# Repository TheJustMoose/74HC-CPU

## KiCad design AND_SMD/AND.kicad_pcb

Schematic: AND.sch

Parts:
C1: 0.1uF; C_0805_2012Metric_Pad1.18x1.45mm_HandSolder
D1: LED; LED_0805_2012Metric_Pad1.15x1.40mm_HandSolder
J1, J2, J3: Conn_01x08_Male; PinHeader_1x08_P2.54mm_Vertical
J4: Conn_01x04_Male; PinHeader_1x04_P2.54mm_Vertical
R1: 1k; R_0805_2012Metric_Pad1.20x1.40mm_HandSolder
U1: 74LS573; SOP-20_7.5x12.8mm_P1.27mm
U2, U3: 74LS08; SO-14_3.9x8.65mm_P1.27mm

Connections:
/A0: J2.8, U2.1
/A7: J2.1, U3.10
/B0: J1.8, U2.2
/B7: J1.1, U3.9
/Latch: J4.4, U1.11 (Load)
/OUT0: J3.8, U1.12 (Q7)
/OUT7: J3.1, U1.19 (Q0)
/~OE: J4.1, R1.2, U1.1 (OE)
GND: C1.2, J4.2, U1.10 (GND), U2.7 (GND), U3.7 (GND)
unnamed: D1.1, R1.1
unnamed: J1.2, U3.12
unnamed: J1.3, U3.4
unnamed: J1.4, U3.1
unnamed: J1.5, U2.9
unnamed: J1.6, U2.12
unnamed: J1.7, U2.4
unnamed: J2.2, U3.13
unnamed: J2.3, U3.5
unnamed: J2.4, U3.2
unnamed: J2.5, U2.10
unnamed: J2.6, U2.13
unnamed: J2.7, U2.5
unnamed: J3.2, U1.18 (Q1)
unnamed: J3.3, U1.17 (Q2)
unnamed: J3.4, U1.16 (Q3)
unnamed: J3.5, U1.15 (Q4)
unnamed: J3.6, U1.14 (Q5)
unnamed: J3.7, U1.13 (Q6)
unnamed: U1.2 (D0), U3.8
unnamed: U1.3 (D1), U3.11
unnamed: U1.4 (D2), U3.6
unnamed: U1.5 (D3), U3.3
unnamed: U1.6 (D4), U2.8
unnamed: U1.7 (D5), U2.11
unnamed: U1.8 (D6), U2.6
unnamed: U1.9 (D7), U2.3
VCC: C1.1, D1.2, J4.3, U1.20 (VCC), U2.14 (VCC), U3.14 (VCC)

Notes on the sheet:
Out
Ctrl

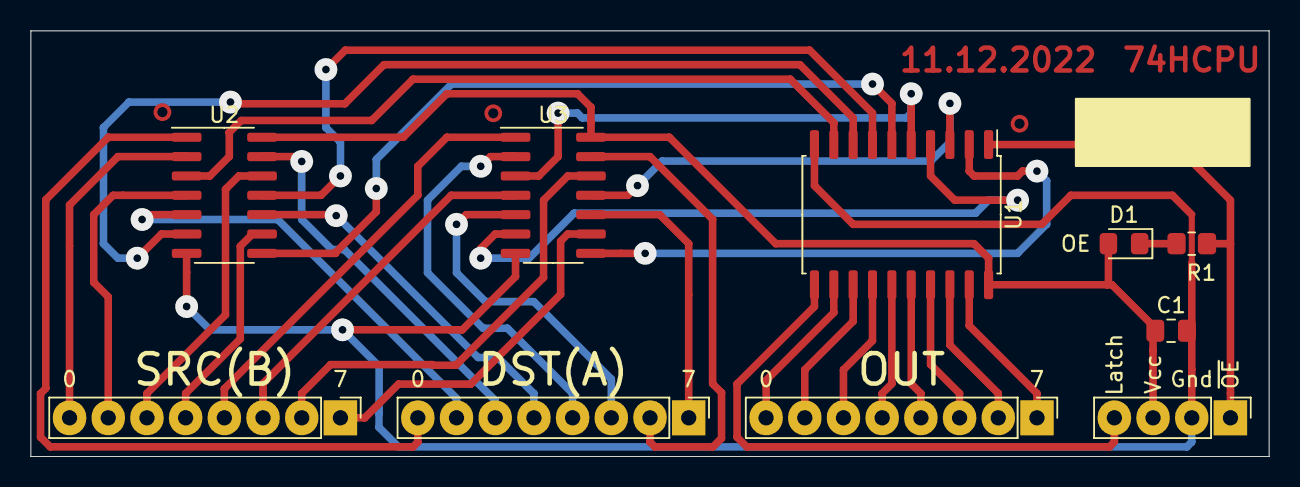
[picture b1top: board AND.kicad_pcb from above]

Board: 2 copper layers, 81.3 x 27.9 mm, 10 parts (0 on the bottom side), 37 nets.

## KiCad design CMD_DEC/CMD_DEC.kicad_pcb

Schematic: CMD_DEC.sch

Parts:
C1, C3, C4, C5, C6: 0.1uF; C_0805_2012Metric_Pad1.18x1.45mm_HandSolder
D1: LED; LED_D5.0mm
H1, H2, H3: MountingHole; MountingHole_3.2mm_M3
J1, J16: Conn_01x04_Male; PinHeader_1x04_P2.54mm_Vertical
J2, J7, J8, J9, J10, J11, J12, J13, J17, J18: Conn_01x01_Male; PinHeader_1x01_P2.54mm_Vertical
J3: Conn_01x05_Male; PinHeader_1x05_P2.54mm_Vertical
J4, J5: Conn_01x08_Male; PinHeader_1x08_P2.54mm_Vertical
J6: Conn_01x02_Male; PinHeader_1x02_P2.54mm_Vertical
J14: Screw_Terminal_01x02; TerminalBlock_Phoenix_MKDS-1,5-2_1x02_P5.00mm_Horizontal
J15: Conn_01x03_Male; PinHeader_1x03_P2.54mm_Vertical
R1, R2: 10k; R_0805_2012Metric_Pad1.20x1.40mm_HandSolder
R5: 1k; R_0805_2012Metric_Pad1.20x1.40mm_HandSolder
U1: 74LS08; DIP-14_W7.62mm_Socket
U2, U4: 74LS138; DIP-16_W7.62mm_Socket
U3: 74LS139; DIP-16_W7.62mm_Socket
U5: 74LS85; DIP-16_W7.62mm_Socket
U6: 74HC00; DIP-14_W7.62mm_Socket

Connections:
/C1: J2.1, U2.5 (E2), U4.5 (E2)
/C2: J13.1, U1.2, U6.10
/CF_EN: J12.1, U6.3
/CMP_EN: J11.1, U6.6
/COP[0]: J1.1, U2.1 (A0), U4.1 (A0), U5.10 (A0)
/COP[1]: J1.2, U2.2 (A1), U4.2 (A1), U5.12 (A1)
/COP[2]: J1.3, U2.3 (A2), U4.3 (A2), U5.13 (A2)
/COP[3]: J1.4, U2.4 (E1), U4.6 (E3), U5.15 (A3)
/LATCH_REG: J8.1, U1.3
/SRC[0]: J6.1, U3.14 (A0)
/SRC[1]: J6.2, U3.13 (A1)
/WILL_WR2REG: J18.1, R5.1, U1.1, U5.7 (Oa<b)
/~ADD: J4.1, U1.4, U2.15 (O0)
/~ADDC: J4.2, U1.5, U2.14 (O1)
/~ADDx: J9.1, U1.6, U6.1
/~AND: J4.3, U2.13 (O2)
/~BRANCH: J5.8, U4.7 (O7)
/~CMP: J5.7, U4.9 (O6), U6.4, U6.5
/~CTRL: J5.6, U4.10 (O5)
/~IN: J5.3, U4.13 (O2)
/~INV: J3.1, U3.12 (O0)
/~LD: J5.2, J17.1, U1.9, U4.14 (O1)
/~LDI: J5.1, U4.15 (O0)
/~LSR: J3.3, U1.13, U3.10 (O2)
/~LSRC: J3.4, U1.12, U3.9 (O3)
/~LSRx: J3.5, U1.11, U6.2
/~MOV: J4.7, U2.9 (O6)
/~MUL: J4.8, U2.7 (O7); also elsewhere on the board
/~OR: J4.4, U2.12 (O3)
/~OUT: J5.4, U4.12 (O3)
/~RAM_CS: J7.1, U1.8
/~RAM_WR: J10.1, U6.8
/~ST: J5.5, U1.10, U4.11 (O4), U6.12, U6.13
/~SWAP: J3.2, U3.11 (O1)
/~UNO: J4.6, U2.10 (O5), U3.15 (E)
/~XOR: J4.5, U2.11 (O4)
GND: C1.2, C3.2, C4.2, C5.2, C6.2, D1.1 (K), J14.2, U1.7 (GND), U2.8 (GND), U3.8 (GND), U4.4 (E1), U4.8 (GND), U5.2 (Ia<b), U5.4 (Ia>b), U5.8 (GND), U5.14 (B2), U6.7 (GND)
unnamed: D1.2 (A), R5.2
unnamed: J15.1, U3.3 (A1)
unnamed: J15.2, U3.2 (A0)
unnamed: J15.3, U3.1 (E)
unnamed: J16.1, U3.4 (O0)
unnamed: J16.2, U3.5 (O1)
unnamed: J16.3, U3.6 (O2)
unnamed: J16.4, U3.7 (O3)
unnamed: R1.1, U2.6 (E3)
unnamed: R2.1, U5.1 (B3), U5.3 (Ia=b), U5.9 (B0), U5.11 (B1)
unnamed: U6.9, U6.11
VCC: C1.1, C3.1, C4.1, C5.1, C6.1, J14.1, R1.2, R2.2, U1.14 (VCC), U2.16 (VCC), U3.16 (VCC), U4.16 (VCC), U5.16 (VCC), U6.14 (VCC)

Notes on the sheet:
< 1011
Signal C1 temporarily disables the outputs to avoid short circuits on commands outputs.
1011

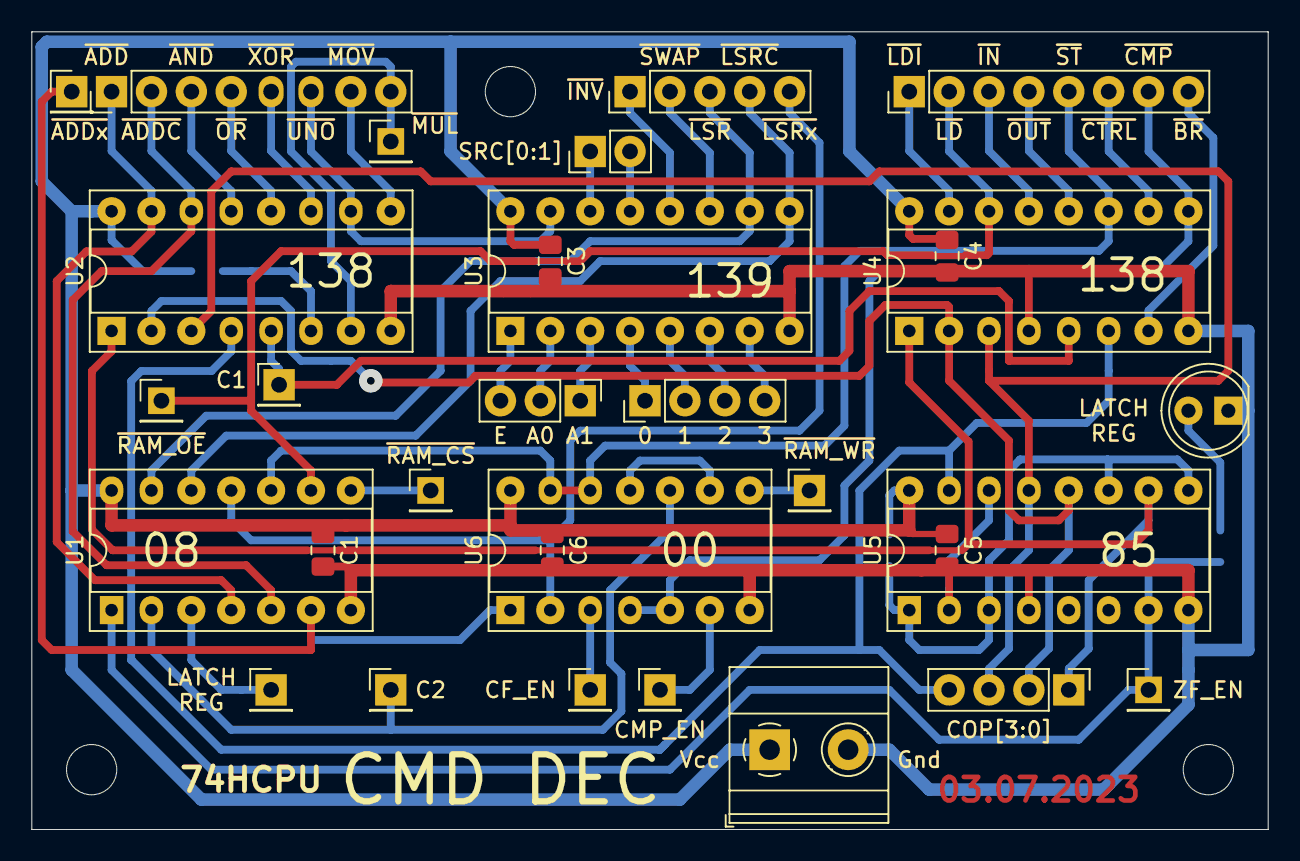
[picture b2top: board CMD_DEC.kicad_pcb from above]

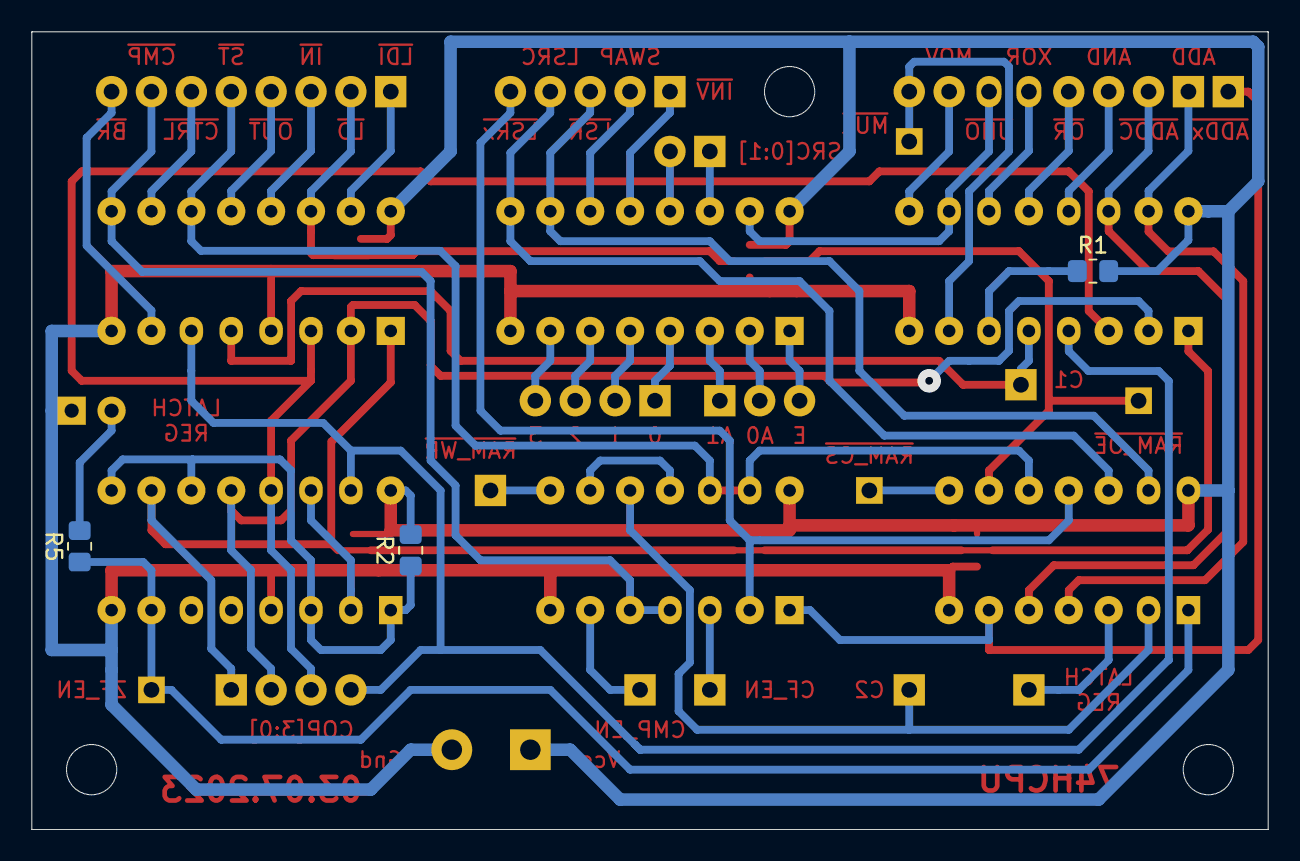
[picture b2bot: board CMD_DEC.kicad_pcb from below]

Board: 2 copper layers, 78.7 x 50.8 mm, 37 parts (3 on the bottom side), 49 nets.

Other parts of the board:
J19: Conn_01x01_Male; PinHeader_1x01_P2.54mm_Vertical

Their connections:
/~MUL: J19.1; also elsewhere on the board

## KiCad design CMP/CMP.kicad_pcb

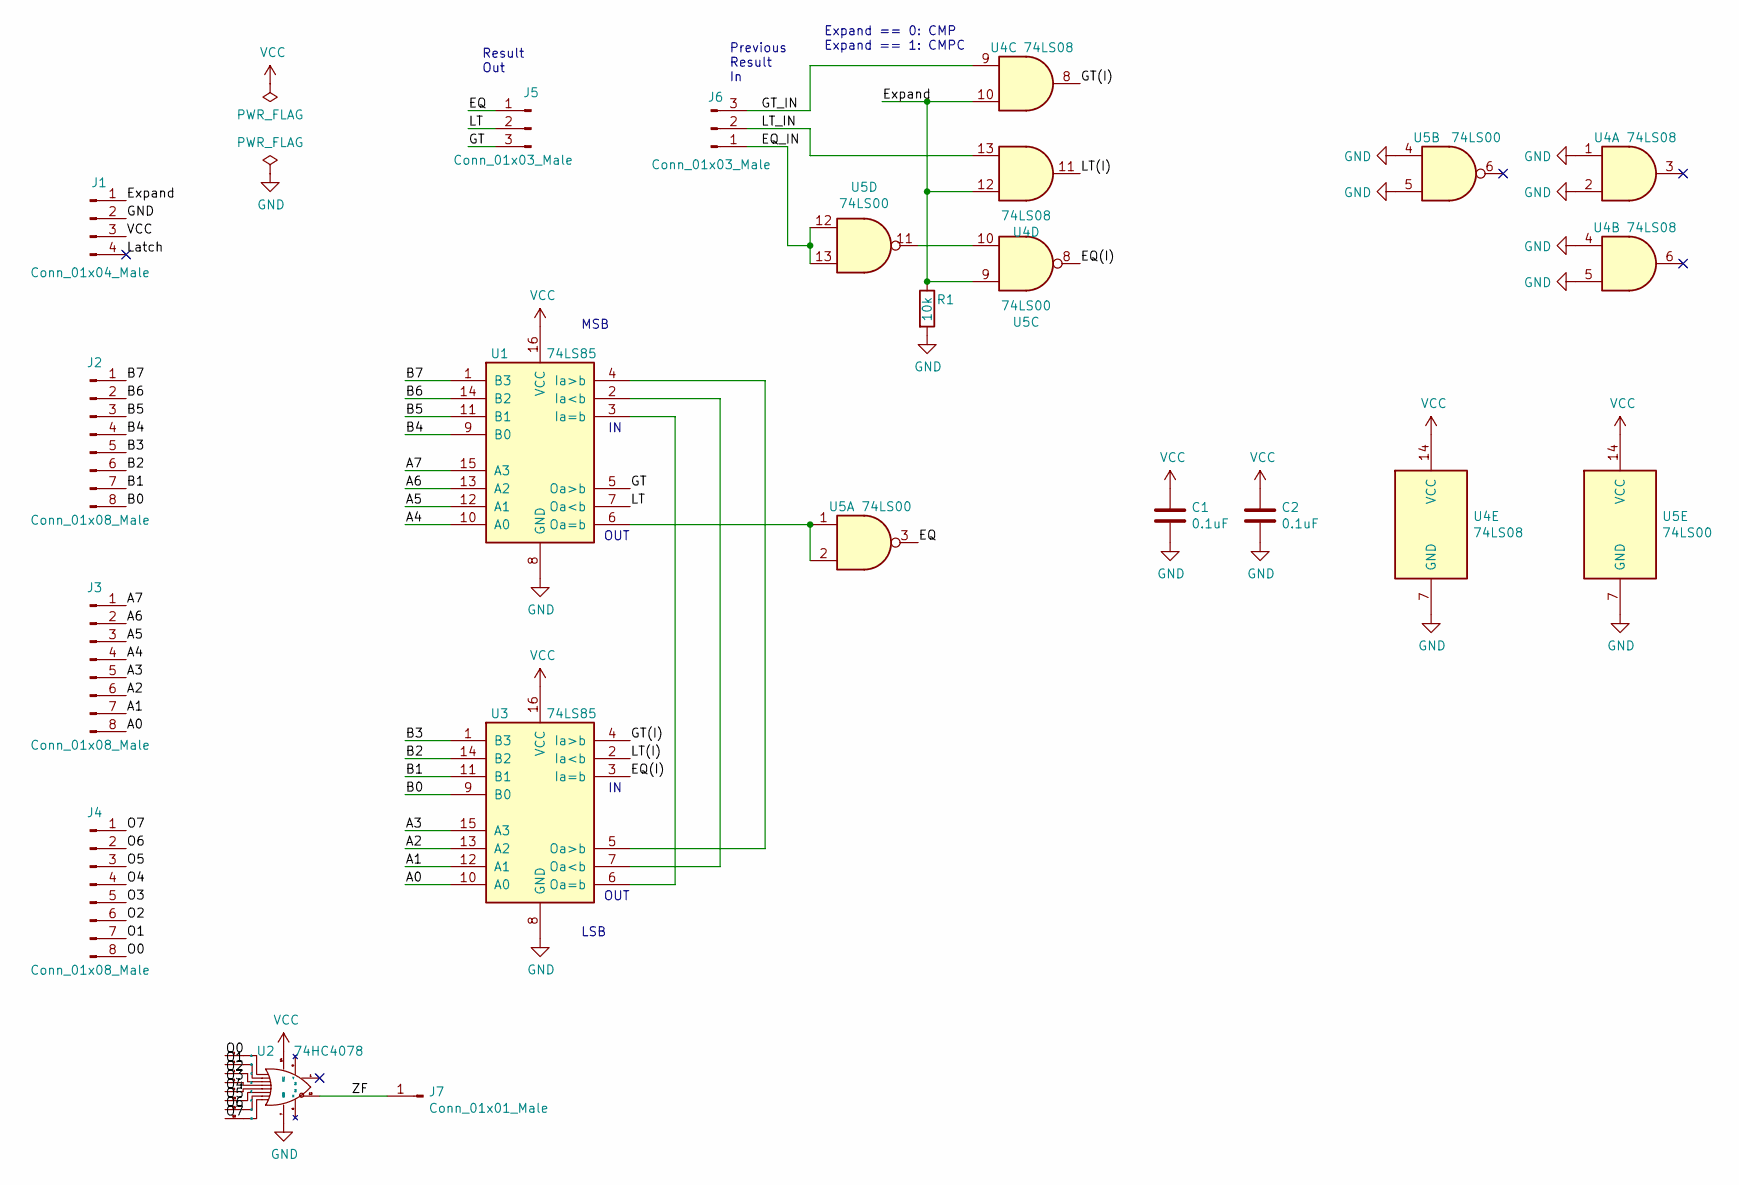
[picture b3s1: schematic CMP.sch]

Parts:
C1, C2: 0.1uF; C_Axial_L3.8mm_D2.6mm_P12.50mm_Horizontal
J1: Conn_01x04_Male; PinHeader_1x04_P2.54mm_Horizontal
J2, J3, J4: Conn_01x08_Male; PinHeader_1x08_P2.54mm_Horizontal
J5, J6: Conn_01x03_Male; PinHeader_1x03_P2.54mm_Horizontal
J7: Conn_01x01_Male; PinHeader_1x01_P2.54mm_Horizontal
R1: 10k; R_0805_2012Metric_Pad1.20x1.40mm_HandSolder
U1, U3: 74LS85; SO-16_3.9x9.9mm_P1.27mm
U2: 74HC4078; SO-14_3.9x8.65mm_P1.27mm
U4: 74LS08; SO-14_3.9x8.65mm_P1.27mm
U5: 74LS00; SO-14_3.9x8.65mm_P1.27mm

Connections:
/A0: J3.8, U3.10 (A0)
/A1: J3.7, U3.12 (A1)
/A2: J3.6, U3.13 (A2)
/A3: J3.5, U3.15 (A3)
/A4: J3.4, U1.10 (A0)
/A5: J3.3, U1.12 (A1)
/A6: J3.2, U1.13 (A2)
/A7: J3.1, U1.15 (A3)
/B0: J2.8, U3.9 (B0)
/B1: J2.7, U3.11 (B1)
/B2: J2.6, U3.14 (B2)
/B3: J2.5, U3.1 (B3)
/B4: J2.4, U1.9 (B0)
/B5: J2.3, U1.11 (B1)
/B6: J2.2, U1.14 (B2)
/B7: J2.1, U1.1 (B3)
/EQ: J5.1, U5.3
/EQ(I): U3.3 (Ia=b), U5.8
/EQ_IN: J6.1, U5.12, U5.13
/Expand: J1.1, R1.1, U4.10, U4.12, U5.9
/GT: J5.3, U1.5 (Oa>b)
/GT(I): U3.4 (Ia>b), U4.8
/GT_IN: J6.3, U4.9
/LT: J5.2, U1.7 (Oa<b)
/LT(I): U3.2 (Ia<b), U4.11
/LT_IN: J6.2, U4.13
/Latch: J1.4
/O0: J4.8, U2.2 (A)
/O1: J4.7, U2.3 (B)
/O2: J4.6, U2.4 (C)
/O3: J4.5, U2.5 (D)
/O4: J4.4, U2.9 (E)
/O5: J4.3, U2.10 (F)
/O6: J4.2, U2.11 (G)
/O7: J4.1, U2.12 (H)
/ZF: J7.1, U2.13 (X)
GND: C1.2, C2.2, J1.2, R1.2, U1.8 (GND), U2.7 (GND), U3.8 (GND), U4.1, U4.2, U4.4, U4.5, U4.7 (GND), U5.4, U5.5, U5.7 (GND)
unnamed: U1.2 (Ia<b), U3.7 (Oa<b)
unnamed: U1.3 (Ia=b), U3.6 (Oa=b)
unnamed: U1.4 (Ia>b), U3.5 (Oa>b)
unnamed: U1.6 (Oa=b), U5.1, U5.2
unnamed: U5.10, U5.11
VCC: C1.1, C2.1, J1.3, U1.16 (VCC), U2.14 (VCC), U3.16 (VCC), U4.14 (VCC), U5.14 (VCC)

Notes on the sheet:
LSB
MSB
OUT
Result Out
Previous Result In
Expand == 0: CMP Expand == 1: CMPC

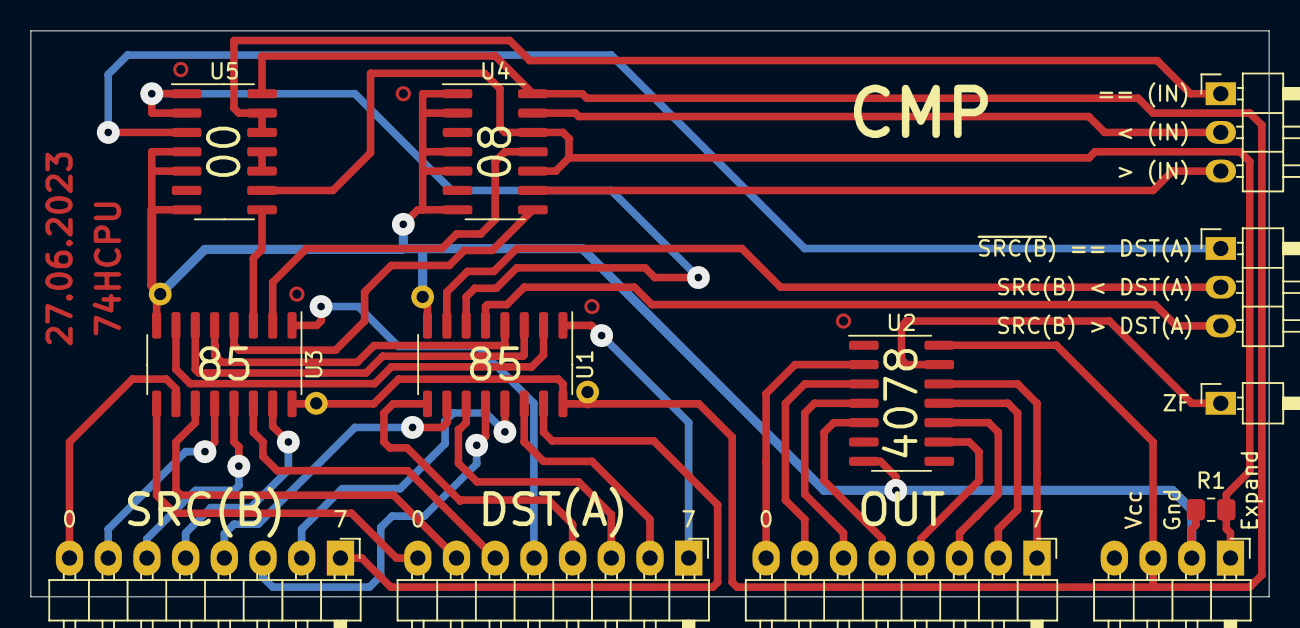
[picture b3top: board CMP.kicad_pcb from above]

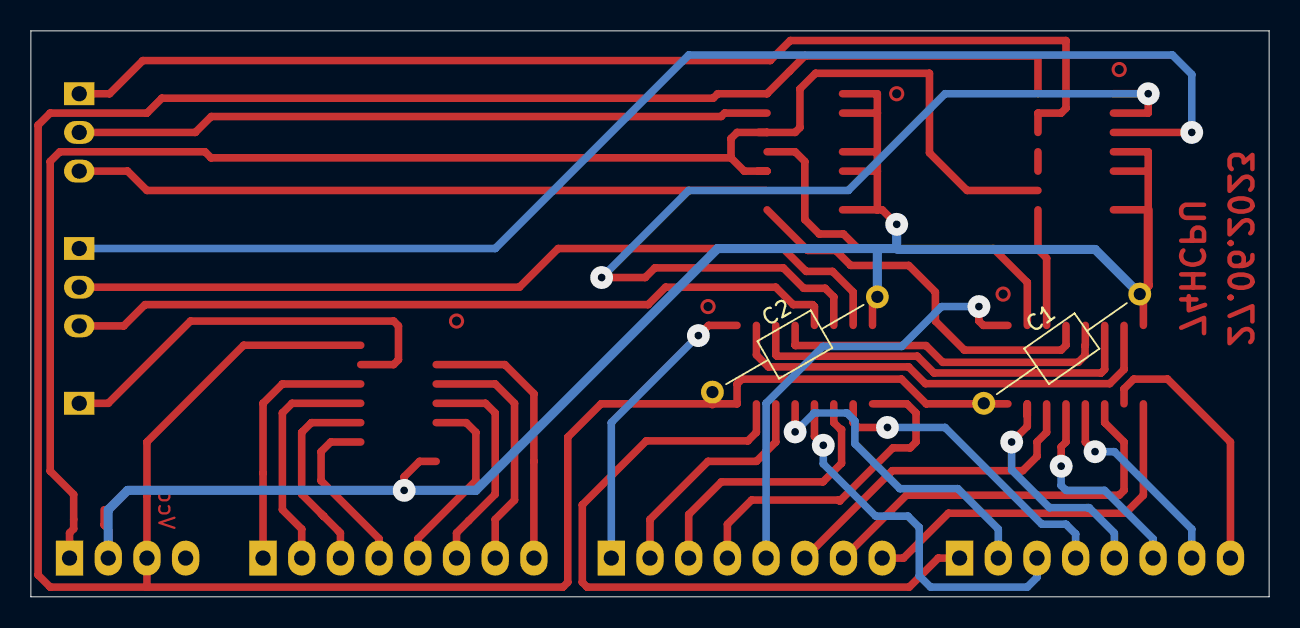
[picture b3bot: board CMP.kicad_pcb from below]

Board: 2 copper layers, 81.3 x 37.1 mm, 15 parts (2 on the bottom side), 42 nets.

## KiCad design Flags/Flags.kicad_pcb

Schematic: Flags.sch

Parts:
C1, C2: 0.1uF; C_Axial_L5.1mm_D3.1mm_P12.50mm_Horizontal
C3: 0.1uF; C_Axial_L5.1mm_D3.1mm_P15.00mm_Horizontal
D1, D2, D3, D4, D5: LED; LED_Rectangular_W5.0mm_H2.0mm
H1, H2, H3, H4: MountingHole; MountingHole_3.2mm_M3
J1: Conn_01x07_Male; PinHeader_1x07_P2.54mm_Vertical
J2: Conn_01x06_Male; PinHeader_1x06_P2.54mm_Vertical
J3: Conn_01x03_Male; PinHeader_1x03_P2.54mm_Vertical
J4, J5, J6, J7: Conn_01x01_Male; PinHeader_1x01_P2.54mm_Vertical
J8: Conn_01x02_Male; PinHeader_1x02_P2.54mm_Vertical
R1, R3: 10k; R_Axial_DIN0207_L6.3mm_D2.5mm_P7.62mm_Horizontal
R2, R4, R5, R6, R7: 1k; R_0805_2012Metric_Pad1.20x1.40mm_HandSolder
U1: 74LS08; DIP-14_W7.62mm_Socket
U2: 74HC74; DIP-14_W7.62mm_Socket
U3: 74LS175; DIP-16_W7.62mm_Socket

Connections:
/C2: J7.1, U1.2, U1.5, U1.10
/CF: J1.5, J5.1, J6.1, U2.6 (~Q)
/CF_EN: J3.1, U1.9
/CMP_EN: J3.3, U1.1
/EQ: J1.3, U3.3 (~Q0)
/GT: J1.2, U3.10 (Q2)
/GT_IN: J2.6, U3.12 (D2)
/LT: J1.1, U3.7 (Q1)
/LT_IN: J2.5, U3.5 (D1)
/ZF: J1.7, U2.9 (Q)
/ZF_EN: J3.2, U1.4
/ZF_IN: J2.3, U2.12 (D)
/~CF: D1.1 (K), J1.4, U2.5 (Q)
/~CF1_IN: J2.1, U1.12
/~CF2_IN: J2.2, U1.13
/~EQ: D4.1 (K), U3.2 (Q0)
/~EQ_IN: J2.4, U3.4 (D0)
/~GT: D5.1 (K), U3.11 (~Q2)
/~LT: D3.1 (K), U3.6 (~Q1)
/~RES_FL: J4.1, U2.4 (~S), U2.13 (~R), U3.1 (~Mr)
/~ZF: D2.1 (K), J1.6, U2.8 (~Q)
GND: C1.2, C2.2, C3.2, J8.2, U1.7 (GND), U2.7 (GND), U3.8 (GND), U3.13 (D3)
unnamed: D1.2 (A), R2.2
unnamed: D2.2 (A), R4.2
unnamed: D3.2 (A), R5.2
unnamed: D4.2 (A), R6.2
unnamed: D5.2 (A), R7.2
unnamed: R1.1, U2.1 (~R)
unnamed: R3.2, U2.10 (~S)
unnamed: U1.3, U3.9 (Cp)
unnamed: U1.6, U2.11 (C)
unnamed: U1.8, U2.3 (C)
unnamed: U1.11, U2.2 (D)
VCC: C1.1, C2.1, C3.1, J8.1, R1.2, R2.1, R3.1, R4.1, R5.1, R6.1, R7.1, U1.14 (VCC), U2.14 (VCC), U3.16 (VCC)

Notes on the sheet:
При сбросе триггера на всех выходах появляется 0. Однако, при сравнении чисел хотя бы один выход должен быть 1! Поэтому выход EQ инвертируется на выходе схемы сравнения.
ADD cmd
LSR cmd
Pins may be connected to:
Inverted CF
Back to the commands: ADD, LSR

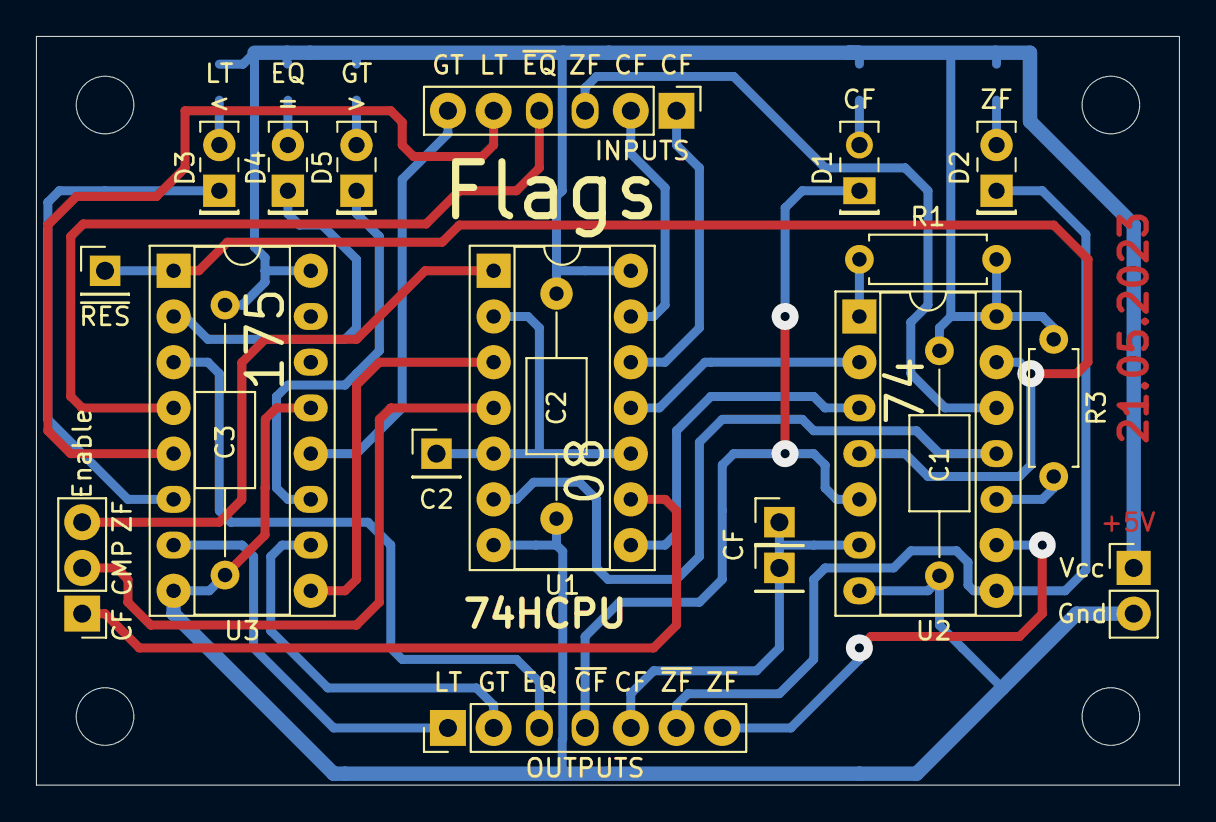
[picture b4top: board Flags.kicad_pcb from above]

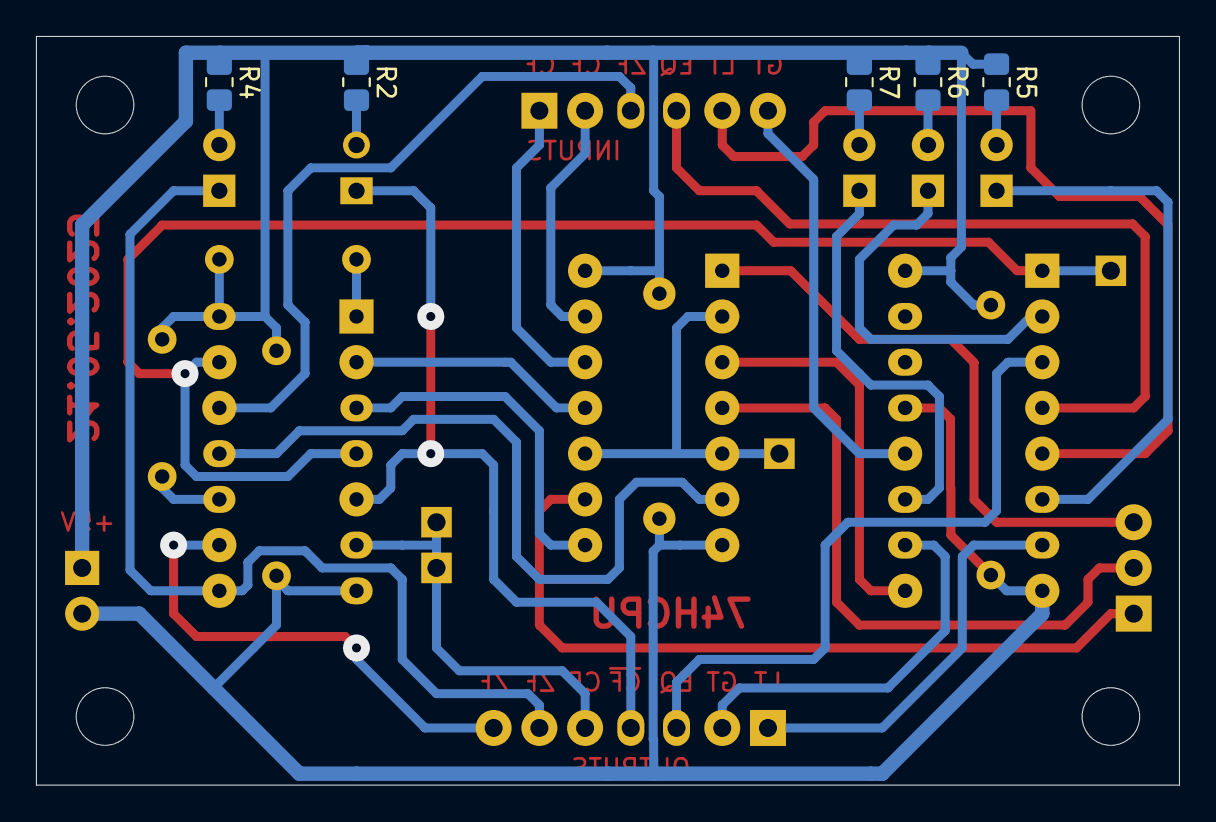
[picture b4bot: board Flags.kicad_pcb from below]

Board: 2 copper layers, 63.5 x 41.6 mm, 30 parts (5 on the bottom side), 34 nets.

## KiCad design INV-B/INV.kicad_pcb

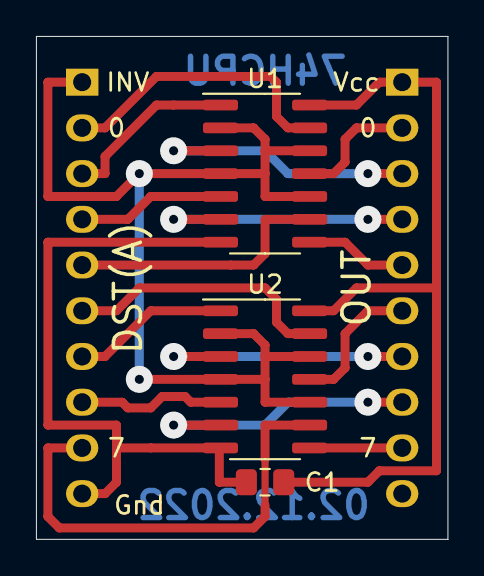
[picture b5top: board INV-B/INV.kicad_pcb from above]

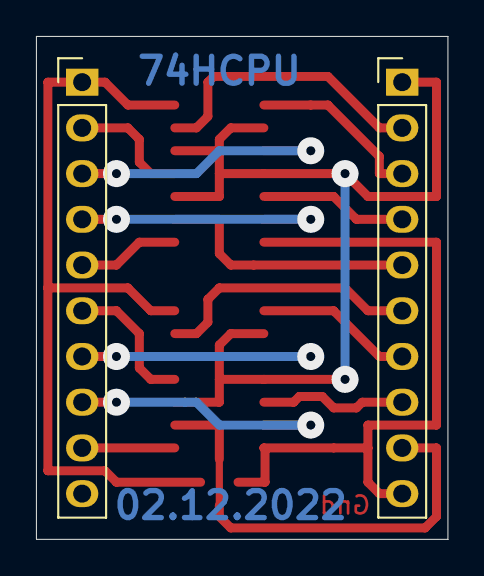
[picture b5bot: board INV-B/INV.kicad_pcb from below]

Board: 2 copper layers, 22.9 x 27.9 mm, 5 parts (2 on the bottom side), 19 nets.

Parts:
C1: 0.1uF; C_0805_2012Metric_Pad1.18x1.45mm_HandSolder
J1, J2: Conn_01x10_Male; PinHeader_1x10_P2.54mm_Vertical
U1, U2: 74HC86; SO-14_3.9x8.65mm_P1.27mm

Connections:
/D0: J1.2, U1.13
/D1: J1.3, U1.1
/D2: J1.4, U1.5
/D3: J1.5, U1.9
/D4: J1.6, U2.13
/D5: J1.7, U2.1
/D6: J1.8, U2.5
/D7: J1.9, U2.9
/INV: J1.1, U1.2, U1.4, U1.10, U1.12, U2.2, U2.4, U2.10, U2.12
/O0: J2.2, U1.11
/O1: J2.3, U1.3
/O2: J2.4, U1.6
/O3: J2.5, U1.8
/O4: J2.6, U2.11
/O5: J2.7, U2.3
/O6: J2.8, U2.6
/O7: J2.9, U2.8
GND: C1.2, J1.10, U1.7, U2.7
VCC: C1.1, J2.1, U1.14, U2.14

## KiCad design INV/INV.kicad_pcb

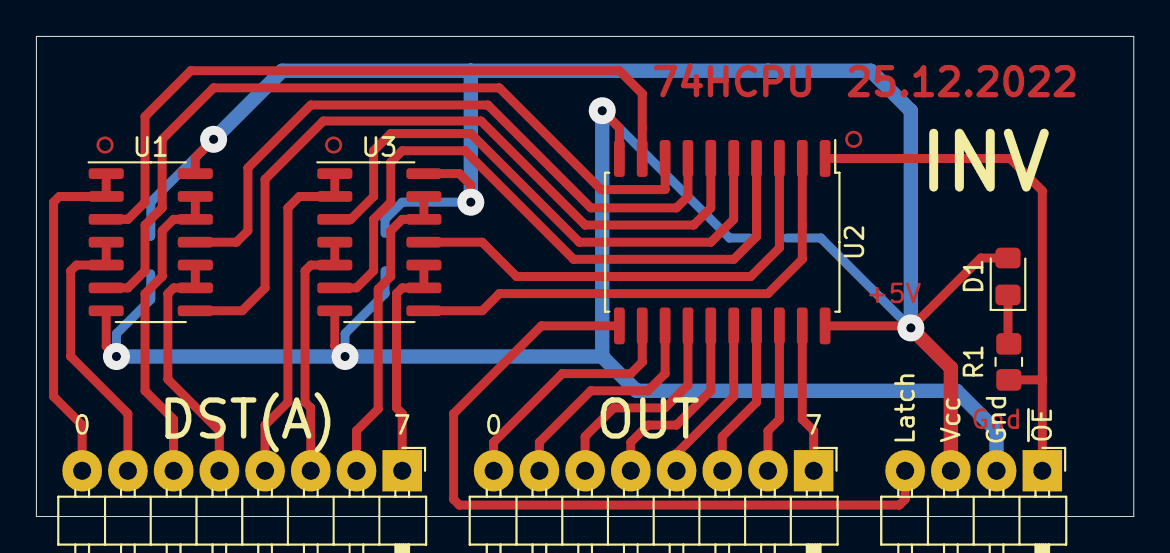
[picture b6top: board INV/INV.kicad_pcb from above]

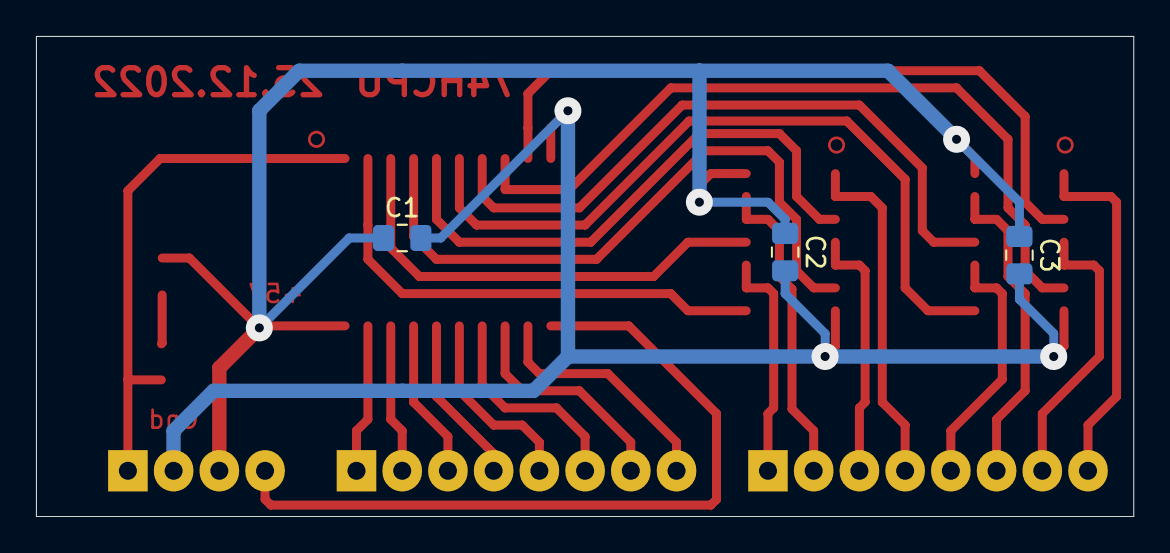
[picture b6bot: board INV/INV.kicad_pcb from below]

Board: 2 copper layers, 61.0 x 26.7 mm, 11 parts (3 on the bottom side), 29 nets.

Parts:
C1, C2, C3: 0.1uF; C_0805_2012Metric_Pad1.18x1.45mm_HandSolder
D1: LED; LED_0805_2012Metric_Pad1.15x1.40mm_HandSolder
J1, J2: Conn_01x08_Male; PinHeader_1x08_P2.54mm_Horizontal
J3: Conn_01x04_Male; PinHeader_1x04_P2.54mm_Horizontal
R1: 1k; R_0805_2012Metric_Pad1.20x1.40mm_HandSolder
U1, U3: 74HC00; SO-14_3.9x8.65mm_P1.27mm
U2: 74LS573; SOIC-20W_7.5x12.8mm_P1.27mm

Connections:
/Latch: J3.4, U2.11
/O0: J2.8, U2.12
/O1: J2.7, U2.13
/O2: J2.6, U2.14
/O3: J2.5, U2.15
/O4: J2.4, U2.16
/O5: J2.3, U2.17
/O6: J2.2, U2.18
/O7: J2.1, U2.19
/~OE: J3.1, R1.2, U2.1
GND: C1.2, C2.2, C3.2, J3.2, U1.7, U2.10, U3.7
unnamed: D1.1, R1.1
unnamed: J1.1, U3.9, U3.10
unnamed: J1.2, U3.12, U3.13
unnamed: J1.3, U3.4, U3.5
unnamed: J1.4, U3.1, U3.2
unnamed: J1.5, U1.9, U1.10
unnamed: J1.6, U1.12, U1.13
unnamed: J1.7, U1.4, U1.5
unnamed: J1.8, U1.1, U1.2
unnamed: U1.3, U2.9
unnamed: U1.6, U2.8
unnamed: U1.8, U2.6
unnamed: U1.11, U2.7
unnamed: U2.2, U3.8
unnamed: U2.3, U3.11
unnamed: U2.4, U3.6
unnamed: U2.5, U3.3
VCC: C1.1, C2.1, C3.1, D1.2, J3.3, U1.14, U2.20, U3.14

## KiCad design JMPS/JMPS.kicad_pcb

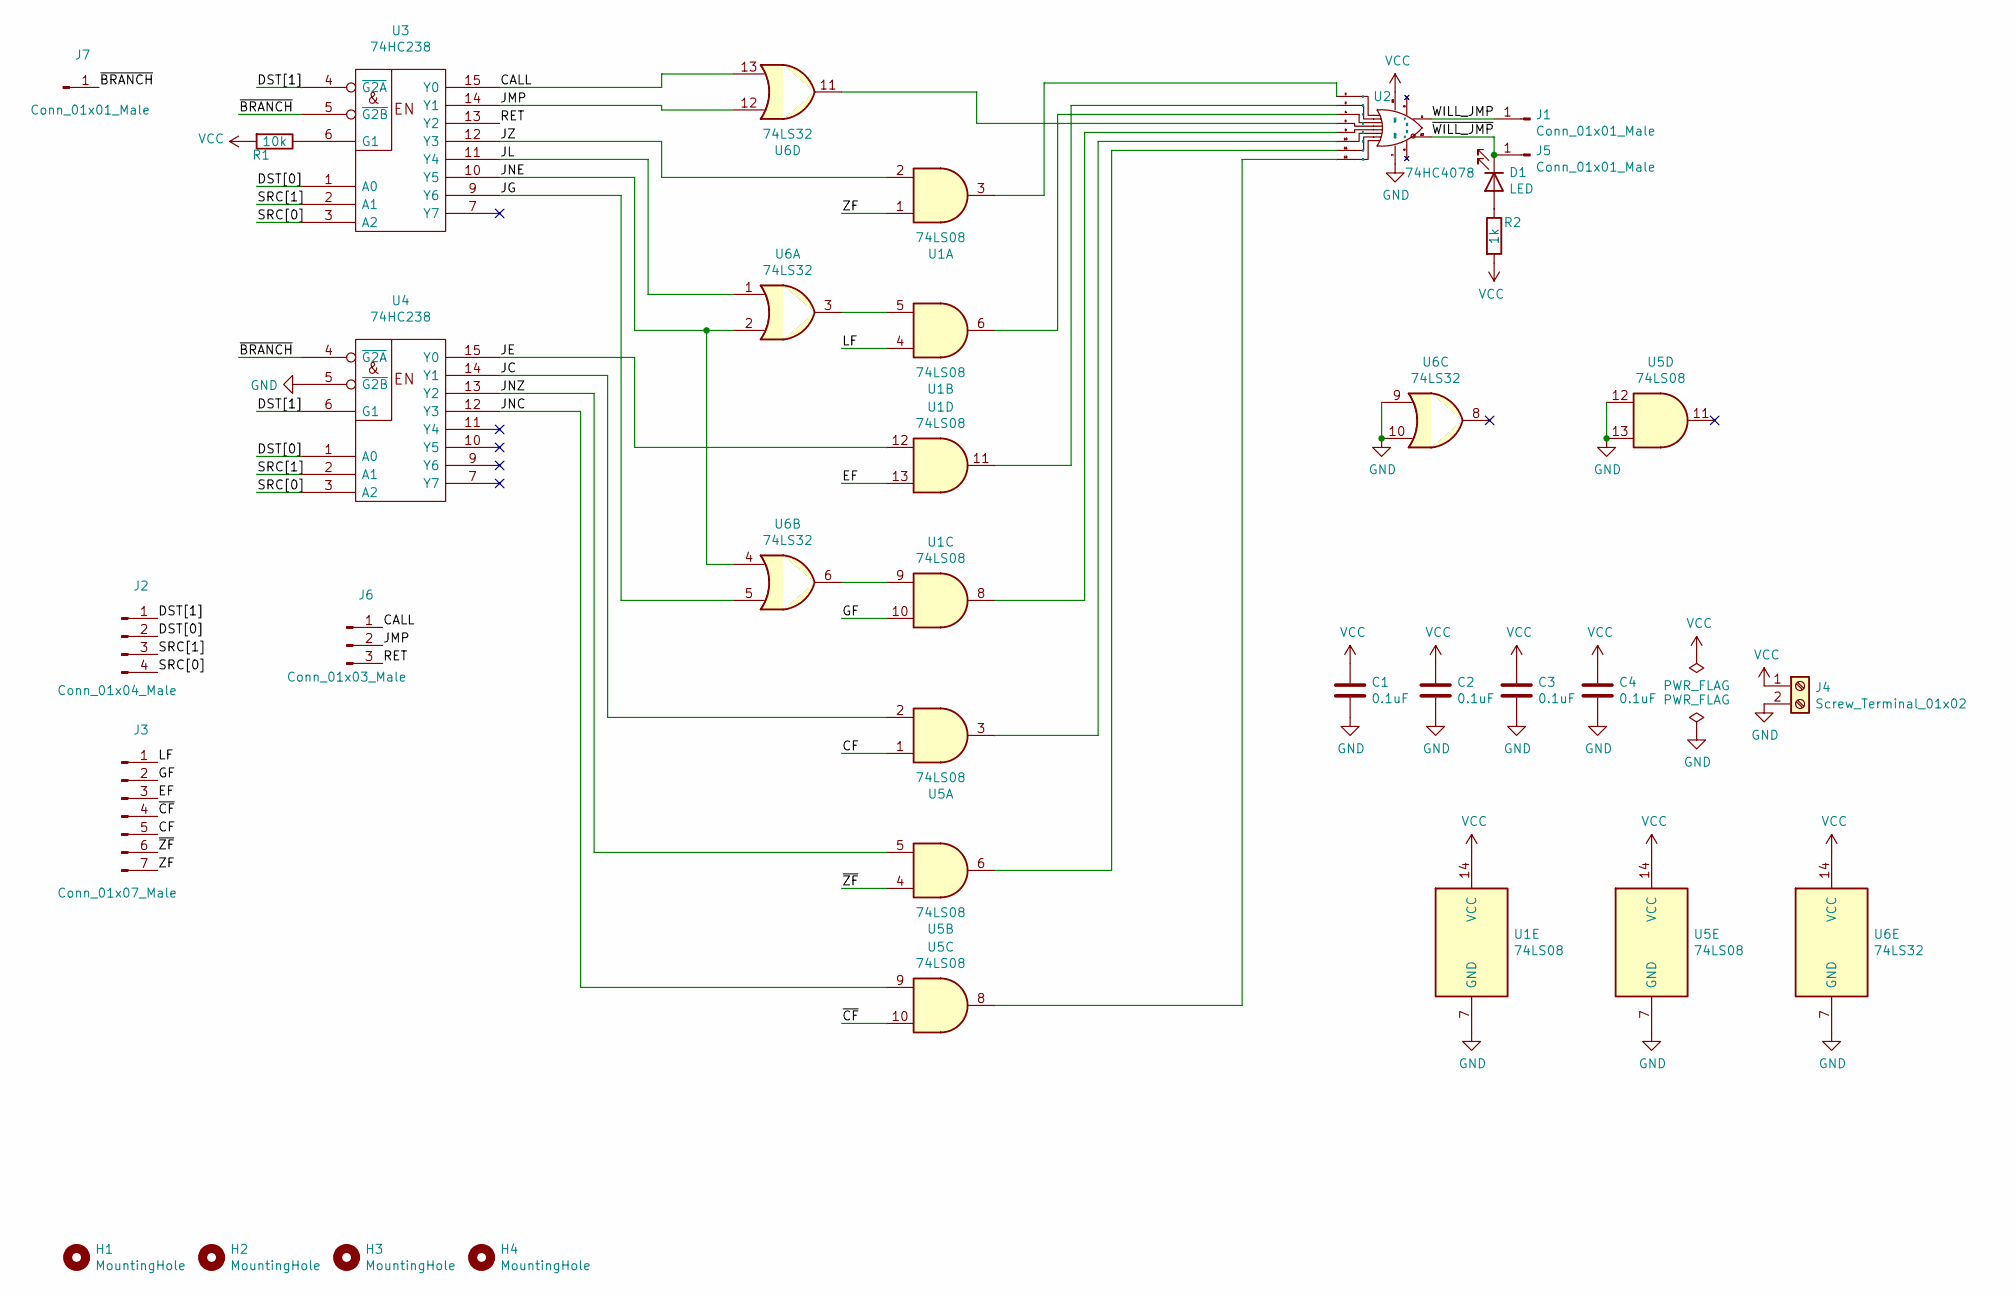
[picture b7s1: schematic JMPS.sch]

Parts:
C1, C2, C3, C4: 0.1uF; C_0805_2012Metric_Pad1.18x1.45mm_HandSolder
D1: LED; LED_D5.0mm
H1, H2, H3, H4: MountingHole; MountingHole_3.2mm_M3
J1, J5, J7: Conn_01x01_Male; PinHeader_1x01_P2.54mm_Vertical
J2: Conn_01x04_Male; PinHeader_1x04_P2.54mm_Vertical
J3: Conn_01x07_Male; PinHeader_1x07_P2.54mm_Vertical
J4: Screw_Terminal_01x02; TerminalBlock_Phoenix_MKDS-1,5-2_1x02_P5.00mm_Horizontal
J6: Conn_01x03_Male; PinHeader_1x03_P2.54mm_Vertical
R1: 10k; R_0805_2012Metric_Pad1.20x1.40mm_HandSolder
R2: 1k; R_0805_2012Metric_Pad1.20x1.40mm_HandSolder
U1, U5: 74LS08; DIP-14_W7.62mm_Socket
U2: 74HC4078; DIP-14_W7.62mm_Socket
U3, U4: 74HC238; DIP-16_W7.62mm_Socket
U6: 74LS32; DIP-14_W7.62mm_Socket

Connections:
/CALL: J6.1, U3.15 (Y0), U6.13
/CF: J3.5, U5.1
/DST[0]: J2.2, U3.1 (A0), U4.1 (A0)
/DST[1]: J2.1, U3.4 (~G2A), U4.6 (G1)
/EF: J3.3, U1.13
/GF: J3.2, U1.10
/JC: U4.14 (Y1), U5.2
/JE: U1.12, U4.15 (Y0)
/JG: U3.9 (Y6), U6.5
/JL: U3.11 (Y4), U6.1
/JMP: J6.2, U3.14 (Y1), U6.12
/JNC: U4.12 (Y3), U5.9
/JNE: U3.10 (Y5), U6.2, U6.4
/JNZ: U4.13 (Y2), U5.5
/JZ: U1.2, U3.12 (Y3)
/LF: J3.1, U1.4
/RET: J6.3, U3.13 (Y2)
/SRC[0]: J2.4, U3.3 (A2), U4.3 (A2)
/SRC[1]: J2.3, U3.2 (A1), U4.2 (A1)
/WILL_JMP: J1.1, U2.1 (Y)
/ZF: J3.7, U1.1
/~BRANCH: J7.1, U3.5 (~G2B), U4.4 (~G2A)
/~CF: J3.4, U5.10
/~WILL_JMP: D1.1 (K), J5.1, U2.13 (X)
/~ZF: J3.6, U5.4
GND: C1.2, C2.2, C3.2, C4.2, J4.2, U1.7 (GND), U2.7 (GND), U3.8 (GND), U4.5 (~G2B), U4.8 (GND), U5.7 (GND), U5.12, U5.13, U6.7 (GND), U6.9, U6.10
unnamed: D1.2 (A), R2.1
unnamed: R1.1, U3.6 (G1)
unnamed: U1.3, U2.2 (A)
unnamed: U1.5, U6.3
unnamed: U1.6, U2.4 (C)
unnamed: U1.8, U2.9 (E)
unnamed: U1.9, U6.6
unnamed: U1.11, U2.3 (B)
unnamed: U2.5 (D), U6.11
unnamed: U2.10 (F), U5.3
unnamed: U2.11 (G), U5.6
unnamed: U2.12 (H), U5.8
VCC: C1.1, C2.1, C3.1, C4.1, J4.1, R1.2, R2.2, U1.14 (VCC), U2.14 (VCC), U3.16 (VCC), U4.16 (VCC), U5.14 (VCC), U6.14 (VCC)

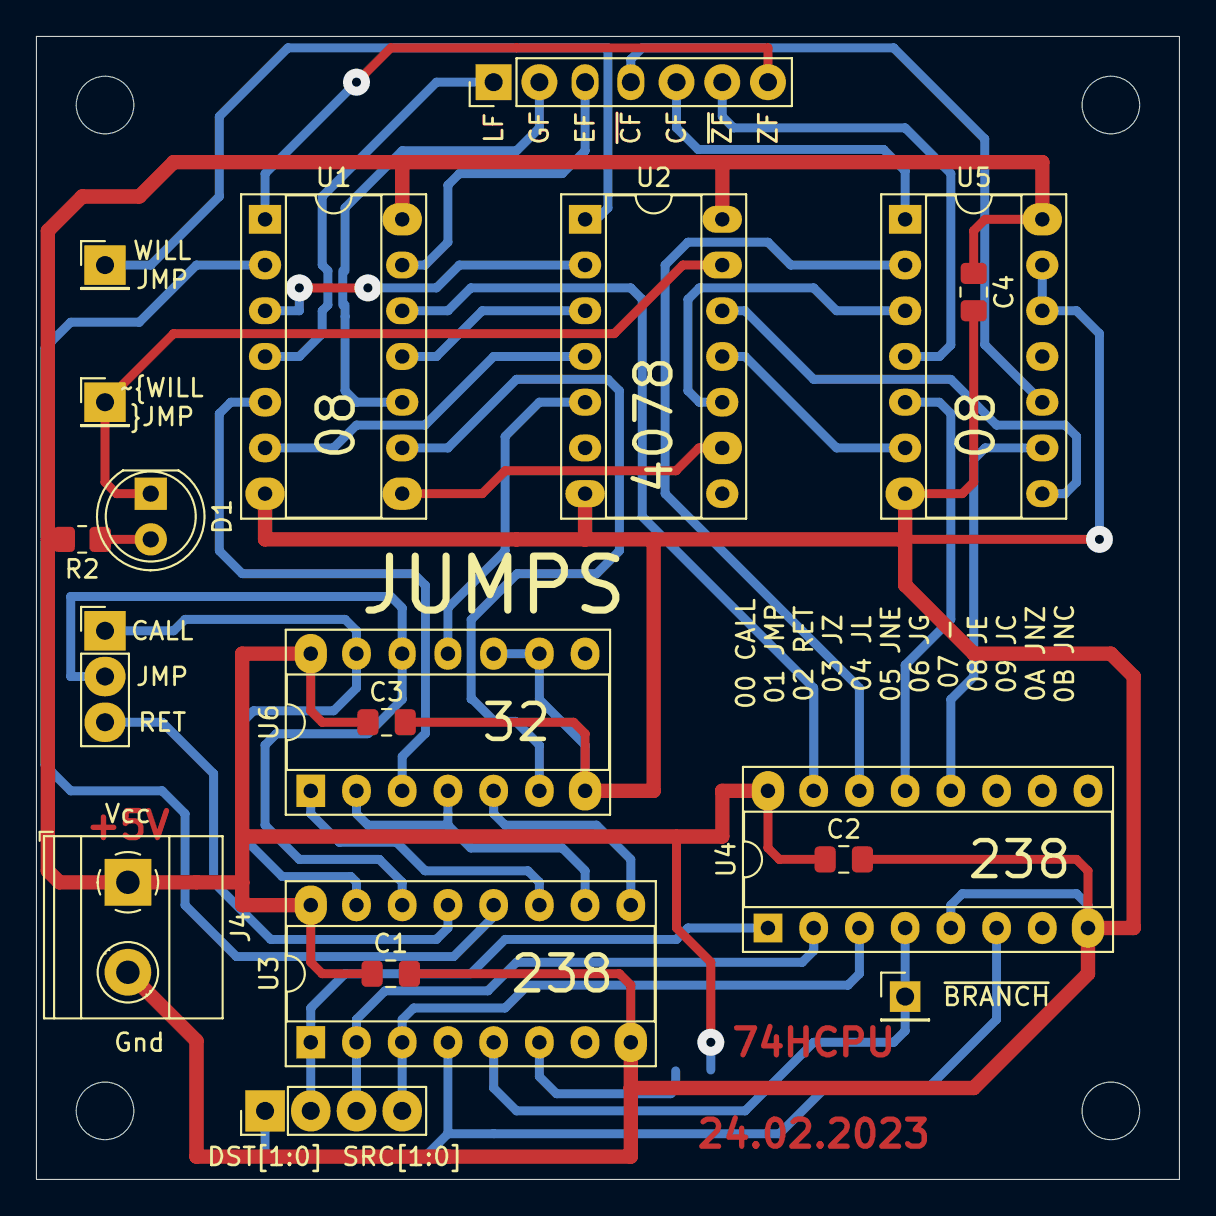
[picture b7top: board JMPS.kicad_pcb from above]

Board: 2 copper layers, 63.5 x 63.5 mm, 24 parts (1 on the bottom side), 39 nets.
